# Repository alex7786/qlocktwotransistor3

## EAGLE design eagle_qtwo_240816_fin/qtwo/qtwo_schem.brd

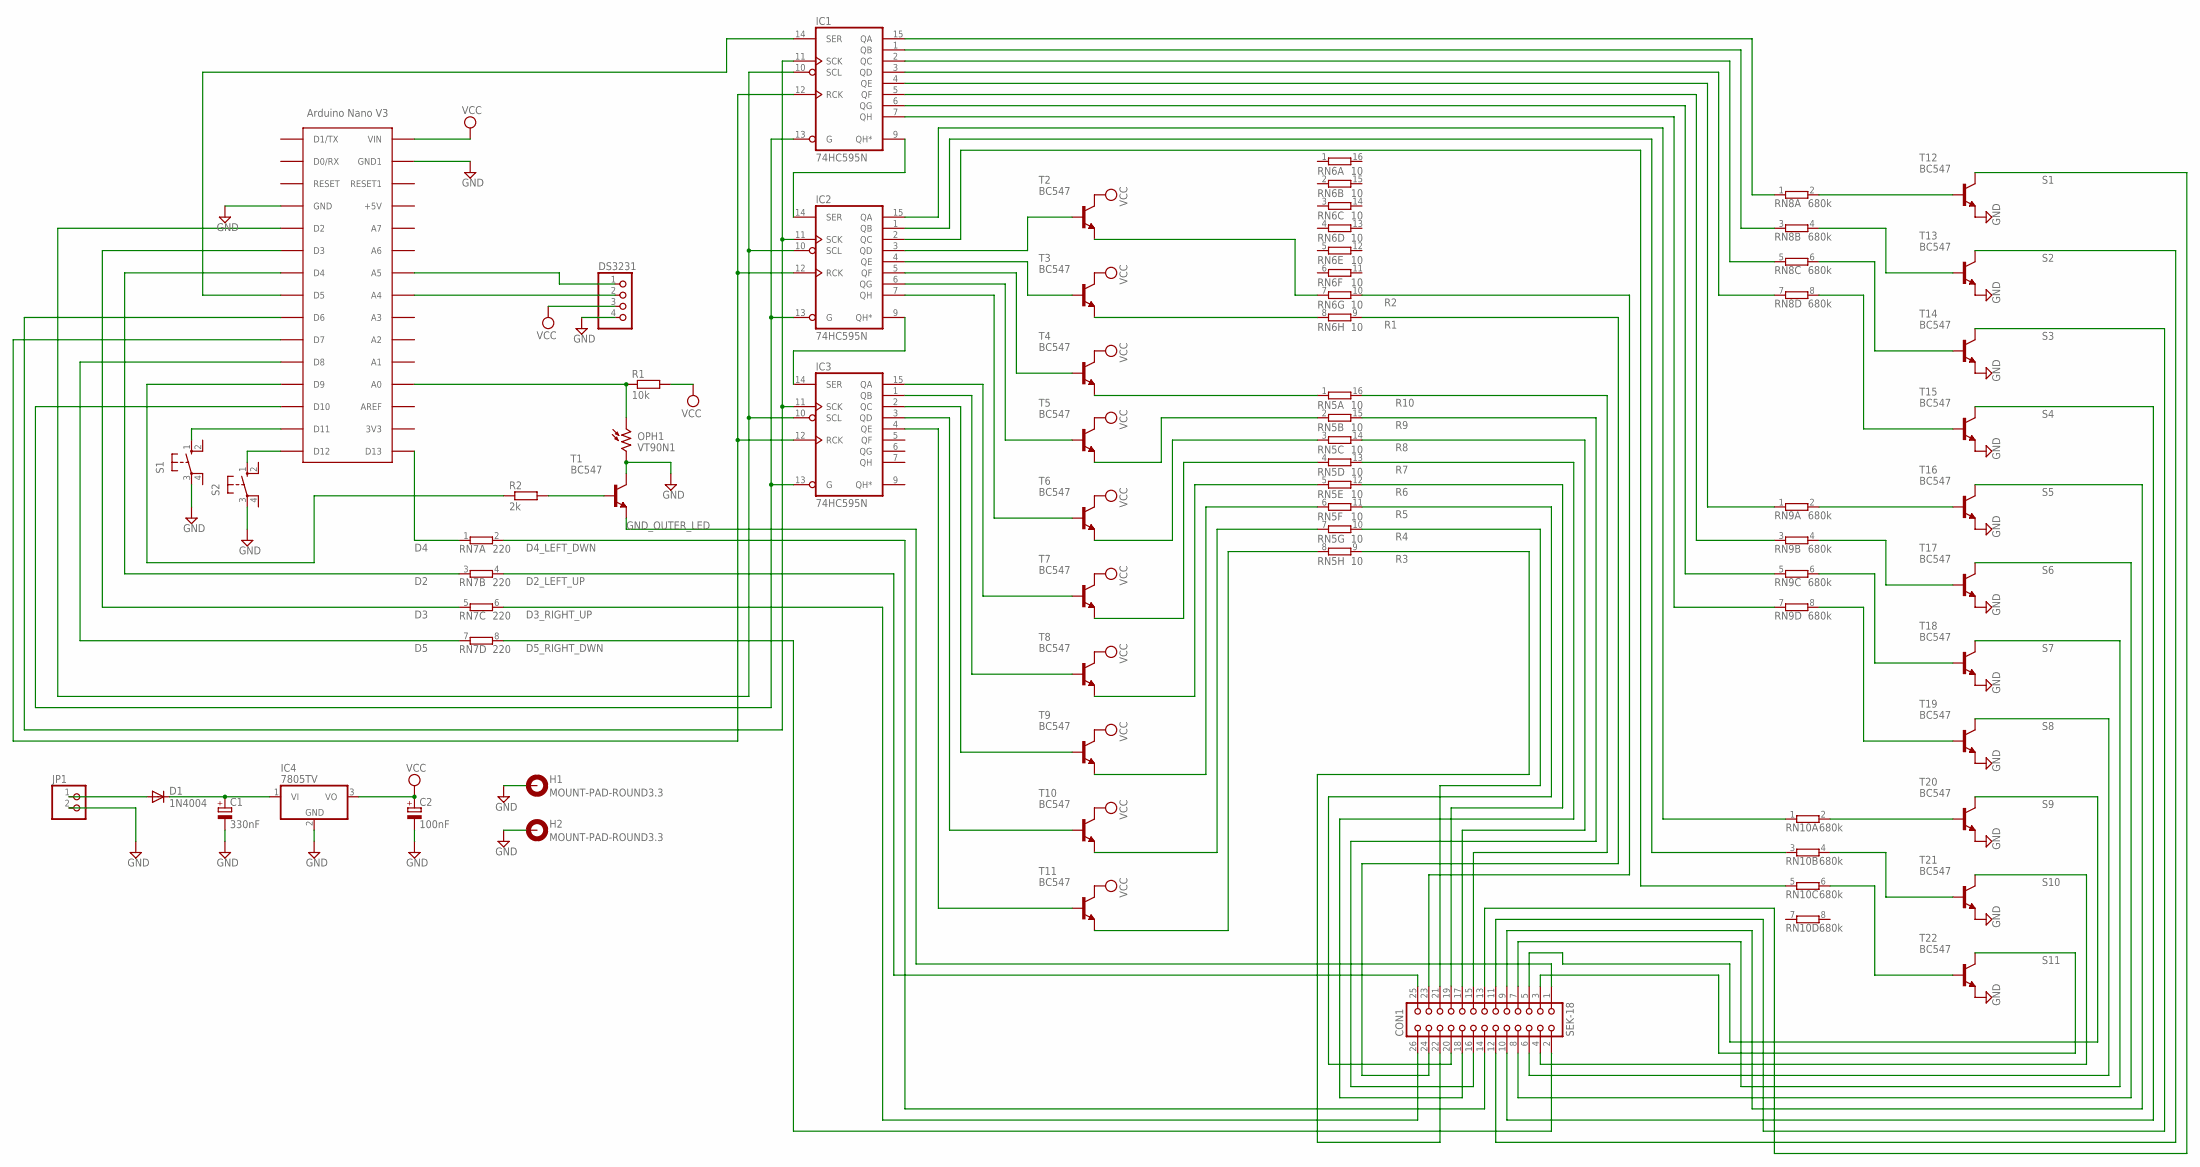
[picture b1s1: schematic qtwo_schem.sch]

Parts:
C1: 330nF; E2,5-6E
C2: 100nF; E2,5-6E
CON1: SEK-18; CON26
D1: 1N4004; DO41-10
DS3231: PINHD-1X4; 1X04
H1, H2: MOUNT-PAD-ROUND3.3; 3,3-PAD
IC1, IC2, IC3: 74HC595N; DIL16
IC4: 7805TV; TO220V
JP1: PINHD-1X2; 1X02
OPH1: VT90N1; VT900
R1: 10k; 0204/7
R2: 2k; 0204/7
RN5, RN6: 10; DIL16
RN7: 220; SIL8
RN8, RN9, RN10: 680k; SIL8
S1, S2: 10-XX; B3F-10XX
T1, T2, T3, T4, T5, T6, T7, T8, T9, T10, T11, T12, T13, T14, T15, T16, T17, T18, T19, T20, T21, T22: BC547; TO92
U$1: ARDUINONANO; PDIP-32

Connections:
D2: RN7.3 (1), U$1.D4
D2_LEFT_UP: CON1.25, RN7.4 (2)
D3: RN7.5 (1), U$1.D3
D3_RIGHT_UP: CON1.26, RN7.6 (2)
D4: RN7.1, U$1.D13
D4_LEFT_DWN: CON1.14, RN7.2
D5: RN7.7 (1), U$1.D8
D5_RIGHT_DWN: CON1.2, RN7.8 (2)
GND: C1.-, C2.-, DS3231.4, H1.B3,3, H2.B3,3, IC1.8 (GND), IC2.8 (GND), IC3.8 (GND), IC4.2 (GND), JP1.2, OPH1.2, S1.3, S2.3, T1.3 (C), T12.1 (E), T13.1 (E), T14.1 (E), T15.1 (E), T16.1 (E), T17.1 (E), T18.1 (E), T19.1 (E), T20.1 (E), T21.1 (E), T22.1 (E), U$1.GND, U$1.GND1
GND_OUTER_LED: CON1.1, T1.1 (E)
unnamed: C1.+, D1.C, IC4.1 (VI)
unnamed: D1.A, JP1.1
unnamed: DS3231.2, U$1.A3 (A4)
unnamed: DS3231.1, U$1.A2 (A5)
unnamed: OPH1.1, R1.1, U$1.A7 (A0)
unnamed: S1.1 (S), U$1.D11
unnamed: S2.1 (S), U$1.D12
unnamed: IC1.10 (SCL), IC2.10 (SCL), IC3.10 (SCL), U$1.D2
unnamed: R2.1, U$1.D9
unnamed: R2.2, T1.2 (B)
unnamed: IC1.13 (G), IC2.13 (G), IC3.13 (G), U$1.D10
unnamed: IC1.11 (SCK), IC2.11 (SCK), IC3.11 (SCK), U$1.D6
unnamed: IC1.12 (RCK), IC2.12 (RCK), IC3.12 (RCK), U$1.D7
unnamed: IC1.14 (SER), U$1.D5
unnamed: IC1.9 (QH*), IC2.14 (SER)
unnamed: IC2.9 (QH*), IC3.14 (SER)
unnamed: IC2.3 (QD), T2.2 (B)
unnamed: IC2.4 (QE), T3.2 (B)
unnamed: IC2.5 (QF), T4.2 (B)
unnamed: IC2.6 (QG), T5.2 (B)
unnamed: IC2.7 (QH), T6.2 (B)
unnamed: IC3.15 (QA), T7.2 (B)
unnamed: IC3.1 (QB), T8.2 (B)
unnamed: IC3.2 (QC), T9.2 (B)
unnamed: IC3.3 (QD), T10.2 (B)
unnamed: IC3.4 (QE), T11.2 (B)
unnamed: RN8.2, T12.2 (B)
unnamed: RN8.4 (2), T13.2 (B)
unnamed: RN8.6 (2), T14.2 (B)
unnamed: RN8.8 (2), T15.2 (B)
unnamed: RN9.2, T16.2 (B)
unnamed: RN9.4 (2), T17.2 (B)
unnamed: RN9.6 (2), T18.2 (B)
unnamed: RN9.8 (2), T19.2 (B)
unnamed: RN10.2, T20.2 (B)
unnamed: RN10.4 (2), T21.2 (B)
unnamed: RN10.6 (2), T22.2 (B)
unnamed: IC1.15 (QA), RN8.1
unnamed: IC1.1 (QB), RN8.3 (1)
unnamed: IC1.2 (QC), RN8.5 (1)
unnamed: IC1.3 (QD), RN8.7 (1)
unnamed: IC1.4 (QE), RN9.1
unnamed: IC1.5 (QF), RN9.3 (1)
unnamed: IC1.6 (QG), RN9.5 (1)
unnamed: IC1.7 (QH), RN9.7 (1)
unnamed: IC2.15 (QA), RN10.1
unnamed: IC2.1 (QB), RN10.3 (1)
unnamed: IC2.2 (QC), RN10.5 (1)
unnamed: RN6.7 (1), T2.1 (E)
unnamed: RN6.8 (1), T3.1 (E)
unnamed: RN5.1, T4.1 (E)
unnamed: RN5.2 (1), T5.1 (E)
unnamed: RN5.3 (1), T6.1 (E)
unnamed: RN5.4 (1), T7.1 (E)
unnamed: RN5.5 (1), T8.1 (E)
unnamed: RN5.6 (1), T9.1 (E)
unnamed: RN5.7 (1), T10.1 (E)
unnamed: RN5.8 (1), T11.1 (E)
R1: CON1.24, RN6.9 (2)
R2: CON1.23, RN6.10 (2)
R3: CON1.22, RN5.9 (2)
R4: CON1.21, RN5.10 (2)
R5: CON1.20, RN5.11 (2)
R6: CON1.19, RN5.12 (2)
R7: CON1.18, RN5.13 (2)
R8: CON1.17, RN5.14 (2)
R9: CON1.16, RN5.15 (2)
R10: CON1.15, RN5.16 (2)
S1: CON1.13, T12.3 (C)
S2: CON1.12, T13.3 (C)
S3: CON1.11, T14.3 (C)
S4: CON1.10, T15.3 (C)
S5: CON1.9, T16.3 (C)
S6: CON1.8, T17.3 (C)
S7: CON1.7, T18.3 (C)
S8: CON1.6, T19.3 (C)
S9: CON1.5, T20.3 (C)
S10: CON1.4, T21.3 (C)
S11: CON1.3, T22.3 (C)
VCC: C2.+, DS3231.3, IC1.16 (VCC), IC2.16 (VCC), IC3.16 (VCC), IC4.3 (VO), R1.2, T2.3 (C), T3.3 (C), T4.3 (C), T5.3 (C), T6.3 (C), T7.3 (C), T8.3 (C), T9.3 (C), T10.3 (C), T11.3 (C), U$1.VIN

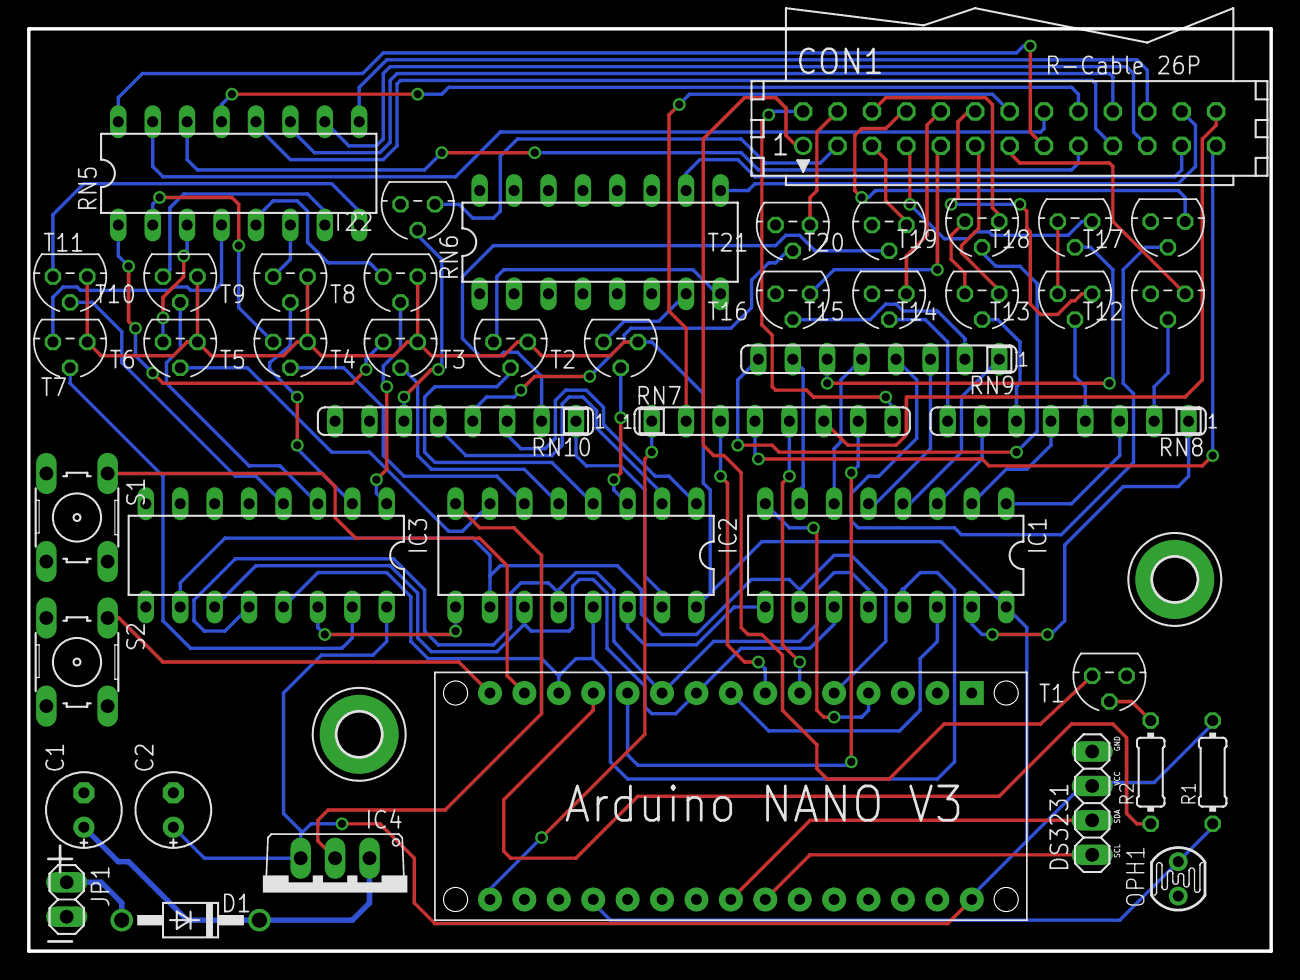
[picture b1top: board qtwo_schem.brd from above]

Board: 2 copper layers, 91.7 x 68.1 mm, 46 parts (0 on the bottom side), 90 nets.

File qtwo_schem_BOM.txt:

Stückliste exportiert aus C:/Users/ad/Documents/eagle/qtwo/qtwo_schem.sch am 06.09.2016 10:56

Part   Value              Device             Package  Description                          MF MPN      OC_FARNELL OC_NEWARK
C1     330nF              CPOL-EUE2,5-6E     E2,5-6E  POLARIZED CAPACITOR, European symbol                                 
C2     100nF              CPOL-EUE2,5-6E     E2,5-6E  POLARIZED CAPACITOR, European symbol                                 
CON1   SEK-18             CON26              CON26    CONNECTOR                                        unknown    unknown  
D1     1N4004             1N4004             DO41-10  DIODE                                                                
DS3231                    PINHD-1X4          1X04     PIN HEADER                                                           
H1     MOUNT-PAD-ROUND3.3 MOUNT-PAD-ROUND3.3 3,3-PAD  MOUNTING PAD, round                                                  
H2     MOUNT-PAD-ROUND3.3 MOUNT-PAD-ROUND3.3 3,3-PAD  MOUNTING PAD, round                                                  
IC1    74HC595N           74HC595N           DIL16    8-bit SHIFT REGISTER, output latch                                   
IC2    74HC595N           74HC595N           DIL16    8-bit SHIFT REGISTER, output latch                                   
IC3    74HC595N           74HC595N           DIL16    8-bit SHIFT REGISTER, output latch                                   
IC4    7805TV             7805TV             TO220V   Positive VOLTAGE REGULATOR                                           
JP1                       PINHD-1X2          1X02     PIN HEADER                                                           
OPH1   VT90N1             VT90N1             VT900    Photoconductive Cell VT900 Series                                    
R1     10k                R-EU_0204/7        0204/7   RESISTOR, European symbol                                            
R2     2k                 R-EU_0204/7        0204/7   RESISTOR, European symbol                                            
RN5    10                 8R-N               DIL16    DIL RESISTOR                                     unknown    unknown  
RN6    10                 8R-N               DIL16    DIL RESISTOR                                     unknown    unknown  
RN7    220                E4R                SIL8     SIL RESISTOR                                     unknown    unknown  
RN8    680k               E4R                SIL8     SIL RESISTOR                                     unknown    unknown  
RN9    680k               E4R                SIL8     SIL RESISTOR                                     unknown    unknown  
RN10   680k               E4R                SIL8     SIL RESISTOR                                     unknown    unknown  
S1                        10-XX              B3F-10XX OMRON SWITCH                            B3F-1000 176432     36M3542  
S2                        10-XX              B3F-10XX OMRON SWITCH                            B3F-1000 176432     36M3542  
T1     BC547              BC547              TO92     NPN TRANSISTOR                                                       
T2     BC547              BC547              TO92     NPN TRANSISTOR                                                       
T3     BC547              BC547              TO92     NPN TRANSISTOR                                                       
T4     BC547              BC547              TO92     NPN TRANSISTOR                                                       
T5     BC547              BC547              TO92     NPN TRANSISTOR                                                       
T6     BC547              BC547              TO92     NPN TRANSISTOR                                                       
T7     BC547              BC547              TO92     NPN TRANSISTOR                                                       
T8     BC547              BC547              TO92     NPN TRANSISTOR                                                       
T9     BC547              BC547              TO92     NPN TRANSISTOR                                                       
T10    BC547              BC547              TO92     NPN TRANSISTOR                                                       
T11    BC547              BC547              TO92     NPN TRANSISTOR                                                       
T12    BC547              BC547              TO92     NPN TRANSISTOR                                                       
T13    BC547              BC547              TO92     NPN TRANSISTOR                                                       
T14    BC547              BC547              TO92     NPN TRANSISTOR                                                       
T15    BC547              BC547              TO92     NPN TRANSISTOR                                                       
T16    BC547              BC547              TO92     NPN TRANSISTOR                                                       
T17    BC547              BC547              TO92     NPN TRANSISTOR                                                       
T18    BC547              BC547              TO92     NPN TRANSISTOR                                                       
T19    BC547              BC547              TO92     NPN TRANSISTOR                                                       
T20    BC547              BC547              TO92     NPN TRANSISTOR                                                       
T21    BC547              BC547              TO92     NPN TRANSISTOR                                                       
T22    BC547              BC547              TO92     NPN TRANSISTOR                                                       
U$1    ARDUINONANO        ARDUINONANO        PDIP-32  Arduino Nano

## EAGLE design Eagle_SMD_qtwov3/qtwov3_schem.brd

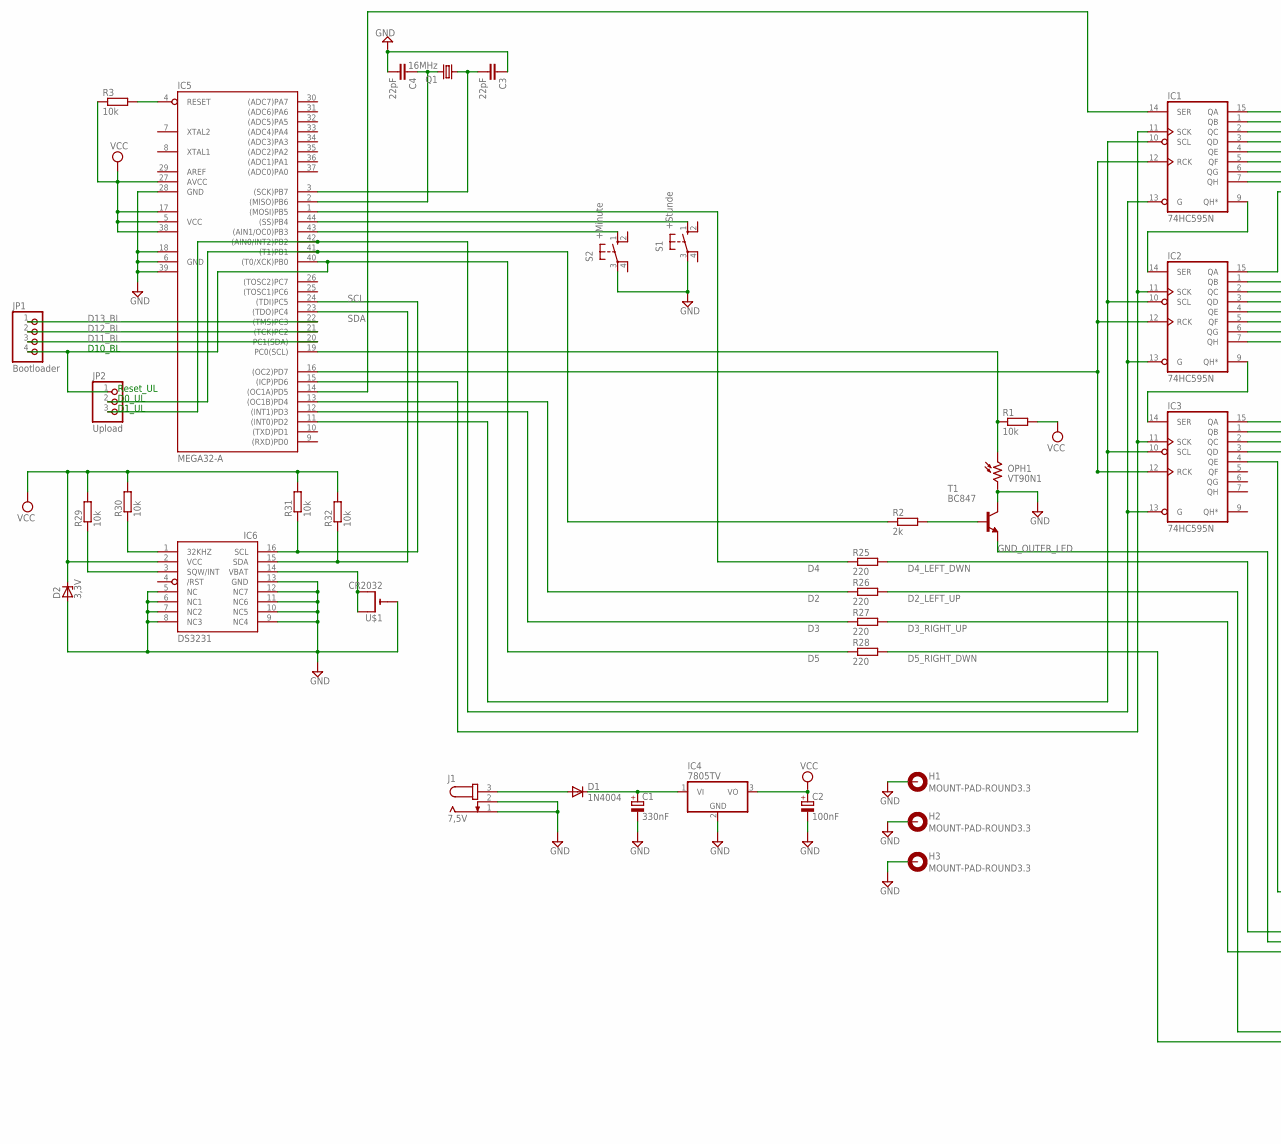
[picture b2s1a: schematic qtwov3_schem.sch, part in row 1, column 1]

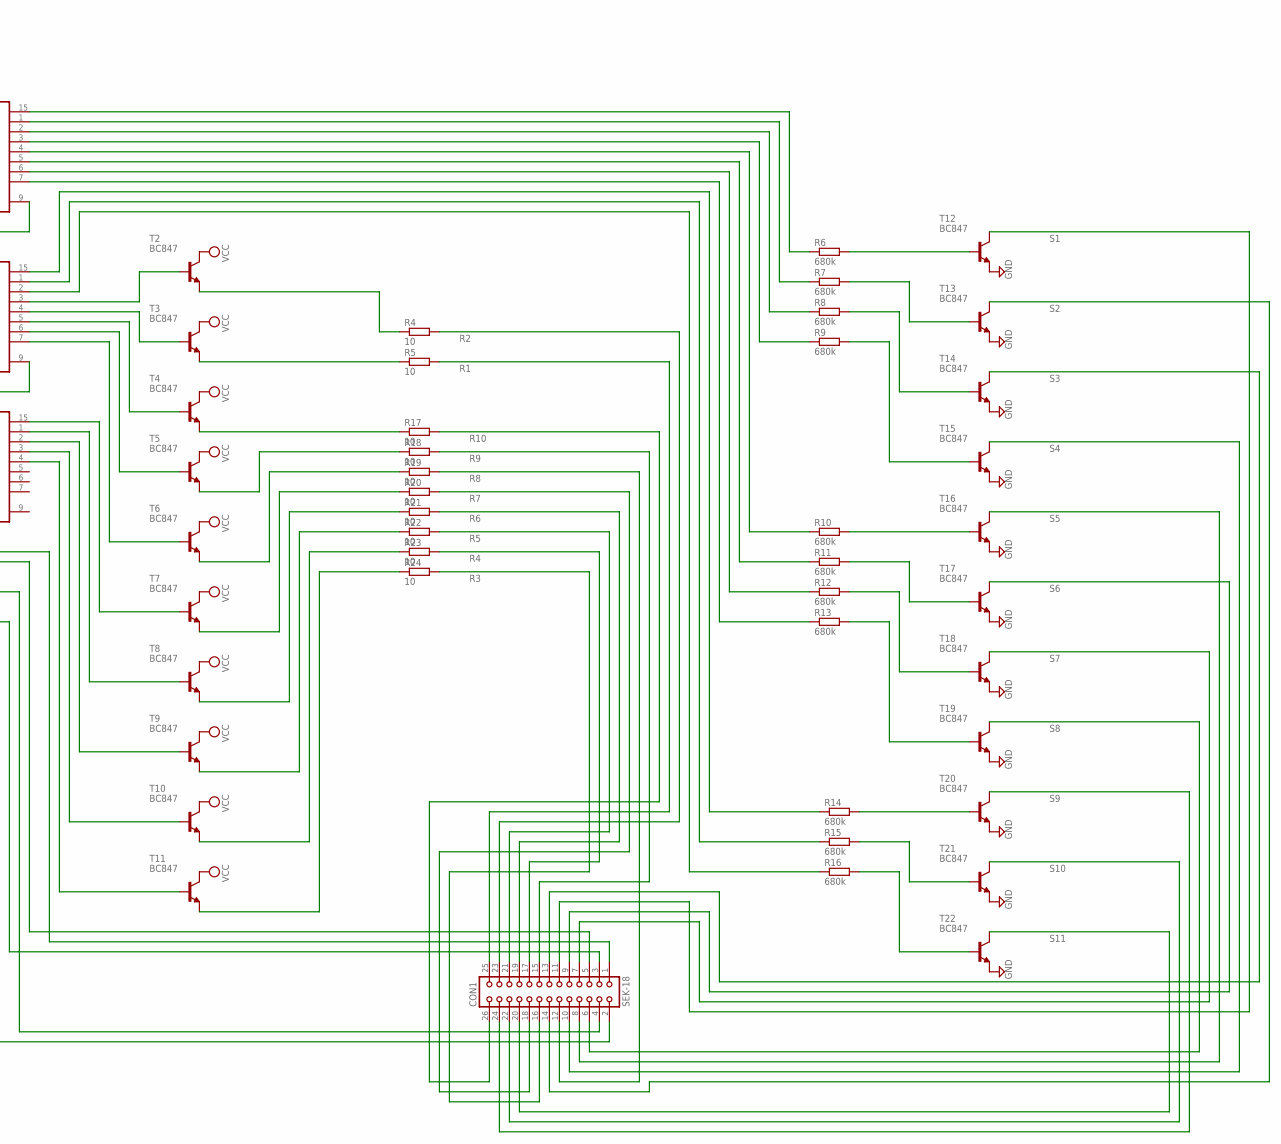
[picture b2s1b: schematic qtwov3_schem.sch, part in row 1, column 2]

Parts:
C1: 330nF; A/3216-18R
C2: 100nF; A/3216-18R
C3, C4: 22pF; C3216
CON1: SEK-18; CON26
D1: 1N4004; DO41-10
D2: 3,3V; P1Z12
H1, H2, H3: MOUNT-PAD-ROUND3.3; 3,3-PAD
IC1, IC2, IC3: 74HC595N; DIL16
IC4: 7805TV; TO220V
IC5: MEGA32-A; TQFP44
IC6: DS3231/SO; SO16W
J1: 7,5V; SPC4078
JP1: Bootloader; 1X04
JP2: Upload; 1X03
OPH1: VT90N1; VT900
Q1: 16MHz; HC49/S
R1, R3, R29, R30, R31, R32: 10k; M3216
R2: 2k; M3216
R4, R5, R17, R18, R19, R20, R21, R22, R23, R24: 10; M3216
R6, R7, R8, R9, R10, R11, R12, R13, R14, R15, R16: 680k; M3216
R25, R26, R27, R28: 220; M3216
S1: +Stunde; B3F-10XX
S2: +Minute; B3F-10XX
T1, T2, T3, T4, T5, T6, T7, T8, T9, T10, T11, T12, T13, T14, T15, T16, T17, T18, T19, T20, T21, T22: BC847; SOT23
U$1: CR2032; CR2032-THRU

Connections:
D2: IC5.13 ((OC1B)PD4), R26.1
D2_LEFT_UP: CON1.4, R26.2
D3: IC5.12 ((INT1)PD3), R27.1
D3_RIGHT_UP: CON1.3, R27.2
D4: IC5.1 ((MOSI)PB5), R25.1
D4_LEFT_DWN: CON1.5, R25.2
D5: IC5.40 ((T0/XCK)PB0), JP1.4, JP2.1, R28.1
D5_RIGHT_DWN: CON1.2, R28.2
D11_BL: IC5.20 (PC1(SDA)), JP1.3
D12_BL: IC5.21 ((TCK)PC2), JP1.2
D13_BL: IC5.22 ((TMS)PC3), JP1.1
GND: C1.-, C2.-, C3.1, C4.2, D2.A, H1.B3,3, H2.B3,3, H3.B3,3, IC1.8 (GND), IC2.8 (GND), IC3.8 (GND), IC4.2 (GND), IC5.6 (GND), IC5.18 (GND1), IC5.28 (GND), IC5.39 (GND2), IC6.5 (NC), IC6.6 (NC1), IC6.7 (NC2), IC6.8 (NC3), IC6.9 (NC4), IC6.10 (NC5), IC6.11 (NC6), IC6.12 (NC7), IC6.13 (GND), J1.1, J1.2, OPH1.2, S1.3, S2.3, T1.3 (C), T12.2 (E), T13.2 (E), T14.2 (E), T15.2 (E), T16.2 (E), T17.2 (E), T18.2 (E), T19.2 (E), T20.2 (E), T21.2 (E), T22.2 (E), U$1.-
GND_OUTER_LED: CON1.1, T1.2 (E)
unnamed: C1.+, D1.C, IC4.1 (VI)
unnamed: D1.A, J1.3
unnamed: IC6.1 (32KHZ), R30.1
unnamed: IC6.3 (SQW/INT), R29.1
unnamed: IC5.19 (PC0(SCL)), OPH1.1, R1.1
unnamed: IC5.44 ((SS)PB4), S1.1 (S)
unnamed: IC5.43 ((AIN1/OC0)PB3), S2.1 (S)
unnamed: IC1.10 (SCL), IC2.10 (SCL), IC3.10 (SCL), IC5.11 ((INT0)PD2)
unnamed: IC5.41 ((T1)PB1), JP2.2, R2.1
unnamed: R2.2, T1.1 (B)
unnamed: IC1.13 (G), IC2.13 (G), IC3.13 (G), IC5.42 ((AIN0/INT2)PB2), JP2.3
unnamed: IC1.11 (SCK), IC2.11 (SCK), IC3.11 (SCK), IC5.15 ((ICP)PD6)
unnamed: IC1.12 (RCK), IC2.12 (RCK), IC3.12 (RCK), IC5.16 ((OC2)PD7)
unnamed: IC1.14 (SER), IC5.14 ((OC1A)PD5)
unnamed: IC1.9 (QH*), IC2.14 (SER)
unnamed: IC2.9 (QH*), IC3.14 (SER)
unnamed: IC2.3 (QD), T2.1 (B)
unnamed: IC2.4 (QE), T3.1 (B)
unnamed: IC2.5 (QF), T4.1 (B)
unnamed: IC2.6 (QG), T5.1 (B)
unnamed: IC2.7 (QH), T6.1 (B)
unnamed: IC3.15 (QA), T7.1 (B)
unnamed: IC3.1 (QB), T8.1 (B)
unnamed: IC3.2 (QC), T9.1 (B)
unnamed: IC3.3 (QD), T10.1 (B)
unnamed: IC3.4 (QE), T11.1 (B)
unnamed: R6.2, T12.1 (B)
unnamed: R7.2, T13.1 (B)
unnamed: R8.2, T14.1 (B)
unnamed: R9.2, T15.1 (B)
unnamed: R10.2, T16.1 (B)
unnamed: R11.2, T17.1 (B)
unnamed: R12.2, T18.1 (B)
unnamed: R13.2, T19.1 (B)
unnamed: R14.2, T20.1 (B)
unnamed: R15.2, T21.1 (B)
unnamed: R16.2, T22.1 (B)
unnamed: IC1.15 (QA), R6.1
unnamed: IC1.1 (QB), R7.1
unnamed: IC1.2 (QC), R8.1
unnamed: IC1.3 (QD), R9.1
unnamed: IC1.4 (QE), R10.1
unnamed: IC1.5 (QF), R11.1
unnamed: IC1.6 (QG), R12.1
unnamed: IC1.7 (QH), R13.1
unnamed: IC2.15 (QA), R14.1
unnamed: IC2.1 (QB), R15.1
unnamed: IC2.2 (QC), R16.1
unnamed: R4.1, T2.2 (E)
unnamed: R5.1, T3.2 (E)
unnamed: R17.1, T4.2 (E)
unnamed: R18.1, T5.2 (E)
unnamed: R19.1, T6.2 (E)
unnamed: R20.1, T7.2 (E)
unnamed: R21.1, T8.2 (E)
unnamed: R22.1, T9.2 (E)
unnamed: R23.1, T10.2 (E)
unnamed: R24.1, T11.2 (E)
unnamed: IC6.14 (VBAT), U$1.+1 (+), U$1.+2 (+1)
unnamed: C4.1, IC5.2 ((MISO)PB6), Q1.2
unnamed: C3.2, IC5.3 ((SCK)PB7), Q1.1
unnamed: IC5.4 (RESET), R3.2
R1: CON1.25, R5.2
R2: CON1.23, R4.2
R3: CON1.16, R24.2
R4: CON1.17, R23.2
R5: CON1.21, R22.2
R6: CON1.19, R21.2
R7: CON1.18, R20.2
R8: CON1.12, R19.2
R9: CON1.15, R18.2
R10: CON1.26, R17.2
S1: CON1.11, T12.3 (C)
S2: CON1.14, T13.3 (C)
S3: CON1.13, T14.3 (C)
S4: CON1.10, T15.3 (C)
S5: CON1.8, T16.3 (C)
S6: CON1.9, T17.3 (C)
S7: CON1.7, T18.3 (C)
S8: CON1.6, T19.3 (C)
S9: CON1.24, T20.3 (C)
S10: CON1.22, T21.3 (C)
S11: CON1.20, T22.3 (C)
SCL: IC5.24 ((TDI)PC5), IC6.16 (SCL), R31.1
SDA: IC5.23 ((TDO)PC4), IC6.15 (SDA), R32.1
VCC: C2.+, D2.C, IC1.16 (VCC), IC2.16 (VCC), IC3.16 (VCC), IC4.3 (VO), IC5.5 (VCC), IC5.17 (VCC1), IC5.27 (AVCC), IC5.38 (VCC2), IC6.2 (VCC), R1.2, R3.1, R29.2, R30.2, R31.2, R32.2, T2.3 (C), T3.3 (C), T4.3 (C), T5.3 (C), T6.3 (C), T7.3 (C), T8.3 (C), T9.3 (C), T10.3 (C), T11.3 (C)

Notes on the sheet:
D10_BL
Reset_UL
D0_UL
D1_UL

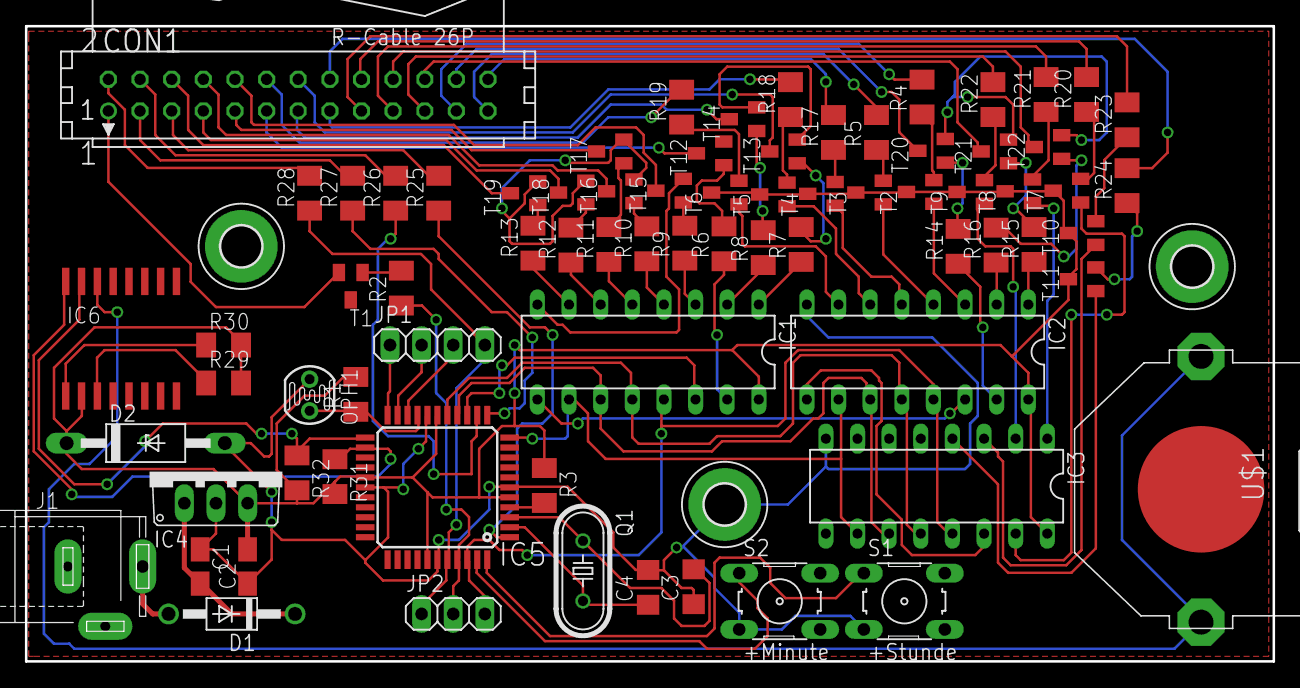
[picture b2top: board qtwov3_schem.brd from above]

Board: 2 copper layers, 100.2 x 51.0 mm, 78 parts (0 on the bottom side), 99 nets.

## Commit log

2016-03-21 :octocat: Added .gitattributes & .gitignore files
2016-03-21 first Upload
2016-04-24 Seconds correction = 0 for ds3231
2016-04-30 change to ds3231
2016-04-30 initial value for hour and minute buffer
2016-05-02 Changed buffer to 0
2016-05-02 few tests
2016-05-16 time rewriting test
2016-05-17 Added picture of I2C adresses and next attempt to correct the ds3231 problem
2016-08-22 Platine und Schema als PDF
2016-08-22 Added BOM
2016-08-23 Added Logo for PCB
2016-08-24 Added Eagle Files
2016-08-30 Added Eagle SMD Variant
2016-09-06 added BOM for qtwo_eagle
2016-09-23 added program qtwo V2
2016-11-04 Added Librarys, corrected code for standalone pcb
2016-12-04 made compatibel to Arduino 1.6.13
